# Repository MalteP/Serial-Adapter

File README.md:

# Serial Adapter

This is a modified version of the famous [Adafruit FTDI Friend](http://www.adafruit.com/products/284), which has the advantage that you can change the signal and power lines separately to be either 3.3V or 5V.

For short circuit protection a PTC fuse (200mA, 0805 package) has been added. There is also a schottky diode (SOD-323 package) in the VCC output path, protecting the USB port from reverse current flow. (Target powered while computer switched off)

It has become a very useful tool during software development on my [DIY Moteino R6](https://lowpowerlab.com/guide/diy-moteino/). While there is also an open sourced [FTDI Adapter](https://github.com/LowPowerLab/FTDIAdapter) board, it lacks of the features mentioned above when compared to the commercial revision R3.

Parts used:
- Fuse F1: 0ZCK0020FF2G (Mouser), FSMD020-0805-R (Reichelt) or equivalent
- Schottky Diode D1: CUS10F30 (Mouser), NSR0320MW2T1G (Reichelt, Mouser) or equivalent

Links:
- [Schematic (PDF)](ftdifriendsch.pdf)
- [Circuit board (Aisler)](https://aisler.net/p/BZEBBFWU)

### License

Adafruit invests time and resources providing this open source design, please support Adafruit and open-source hardware by purchasing products from [Adafruit](https://www.adafruit.com)!

Designed by Limor Fried/Ladyada for Adafruit Industries.

Creative Commons Attribution/Share-Alike, all text above must be included in any redistribution. See license.txt for additional details.

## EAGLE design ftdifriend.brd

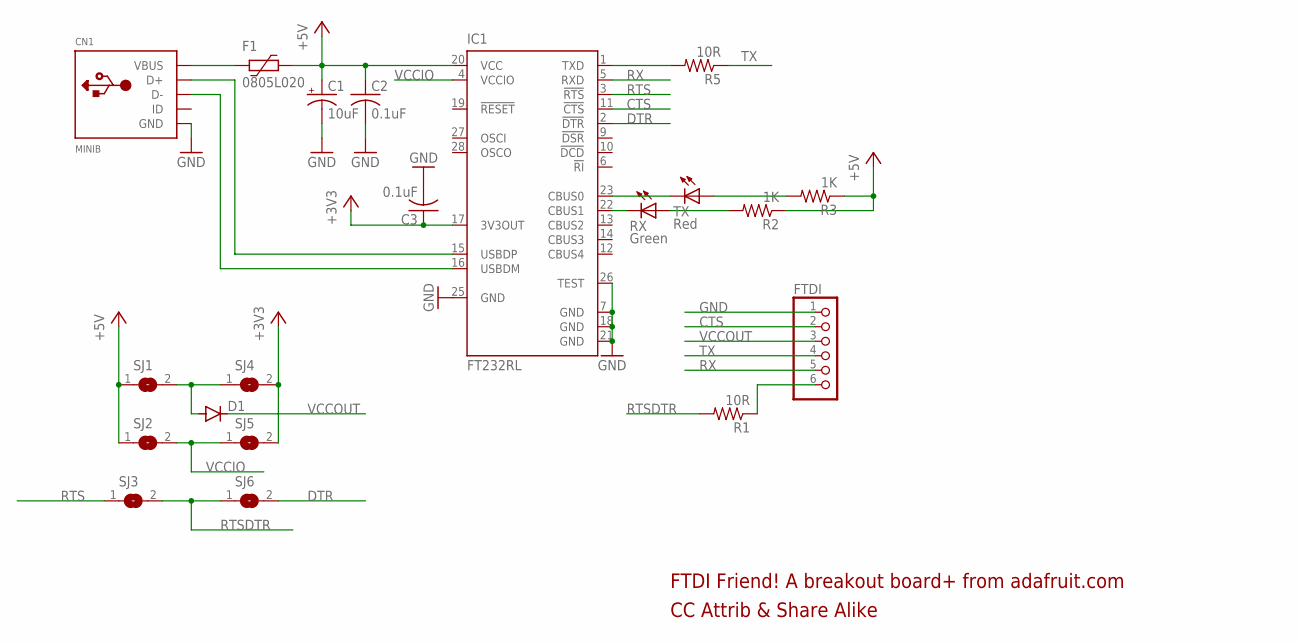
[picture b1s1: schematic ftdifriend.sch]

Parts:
C1: 10uF; A/3216-18R
C2, C3: 0.1uF; C0805K
CN1: MINIB; USB-MINIB
D1: CUS10F30; SOD323-W
F1: 0805L020; 0805L
FTDI: PINHD-1X6CB; 1X06-CLEANBIG
IC1: FT232RL; SSOP28
R1, R5: 10R; R0805
R2, R3: 1K; R0805
RX: Green; CHIP-LED0805
SJ1, SJ2, SJ3, SJ4, SJ5, SJ6: SJ
TX: Red; CHIP-LED0805

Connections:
+3V3: C3.1, IC1.17 (3V3OUT), SJ4.2, SJ5.2
+5V: C1.+, C2.1, F1.1, IC1.20 (VCC), R2.1, R3.1, SJ1.1, SJ2.1
CTS: FTDI.2, IC1.11 (!CTS)
D+: CN1.D+, IC1.15 (USBDP)
D-: CN1.D-, IC1.16 (USBDM)
DTR: IC1.2 (!DTR), SJ6.2
GND: C1.-, C2.2, C3.2, CN1.GND, FTDI.1, IC1.7 (GND), IC1.18 (GND), IC1.21 (GND), IC1.25 (GND), IC1.26 (TEST)
unnamed: FTDI.6, R1.1
unnamed: IC1.1 (TXD), R5.2
unnamed: IC1.23 (CBUS0), TX.C
unnamed: IC1.22 (CBUS1), RX.C
unnamed: R2.2, RX.A
unnamed: R3.2, TX.A
unnamed: CN1.VBUS, F1.2
RTS: IC1.3 (!RTS), SJ3.1
RTSDTR: R1.2, SJ3.2, SJ6.1
RX: FTDI.5, IC1.5 (RXD)
TX: FTDI.4, R5.1
VCCIO: IC1.4 (VCCIO), SJ2.2, SJ5.1
VCCOUT: D1.C, FTDI.3
VCCOUT_A: D1.A, SJ1.2, SJ4.1

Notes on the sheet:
CC Attrib & Share Alike
FTDI Friend! A breakout board+ from adafruit.com

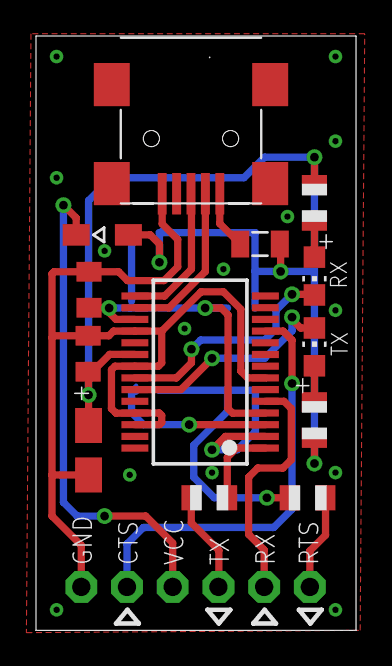
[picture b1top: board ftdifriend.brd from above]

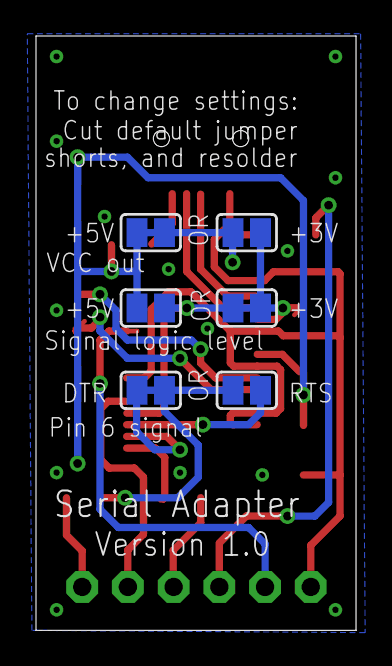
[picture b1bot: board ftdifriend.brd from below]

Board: 2 copper layers, 17.8 x 33.0 mm, 20 parts (6 on the bottom side), 21 nets.

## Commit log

2023-04-01 Update files to modified version with PTC fuse & schottky diode
